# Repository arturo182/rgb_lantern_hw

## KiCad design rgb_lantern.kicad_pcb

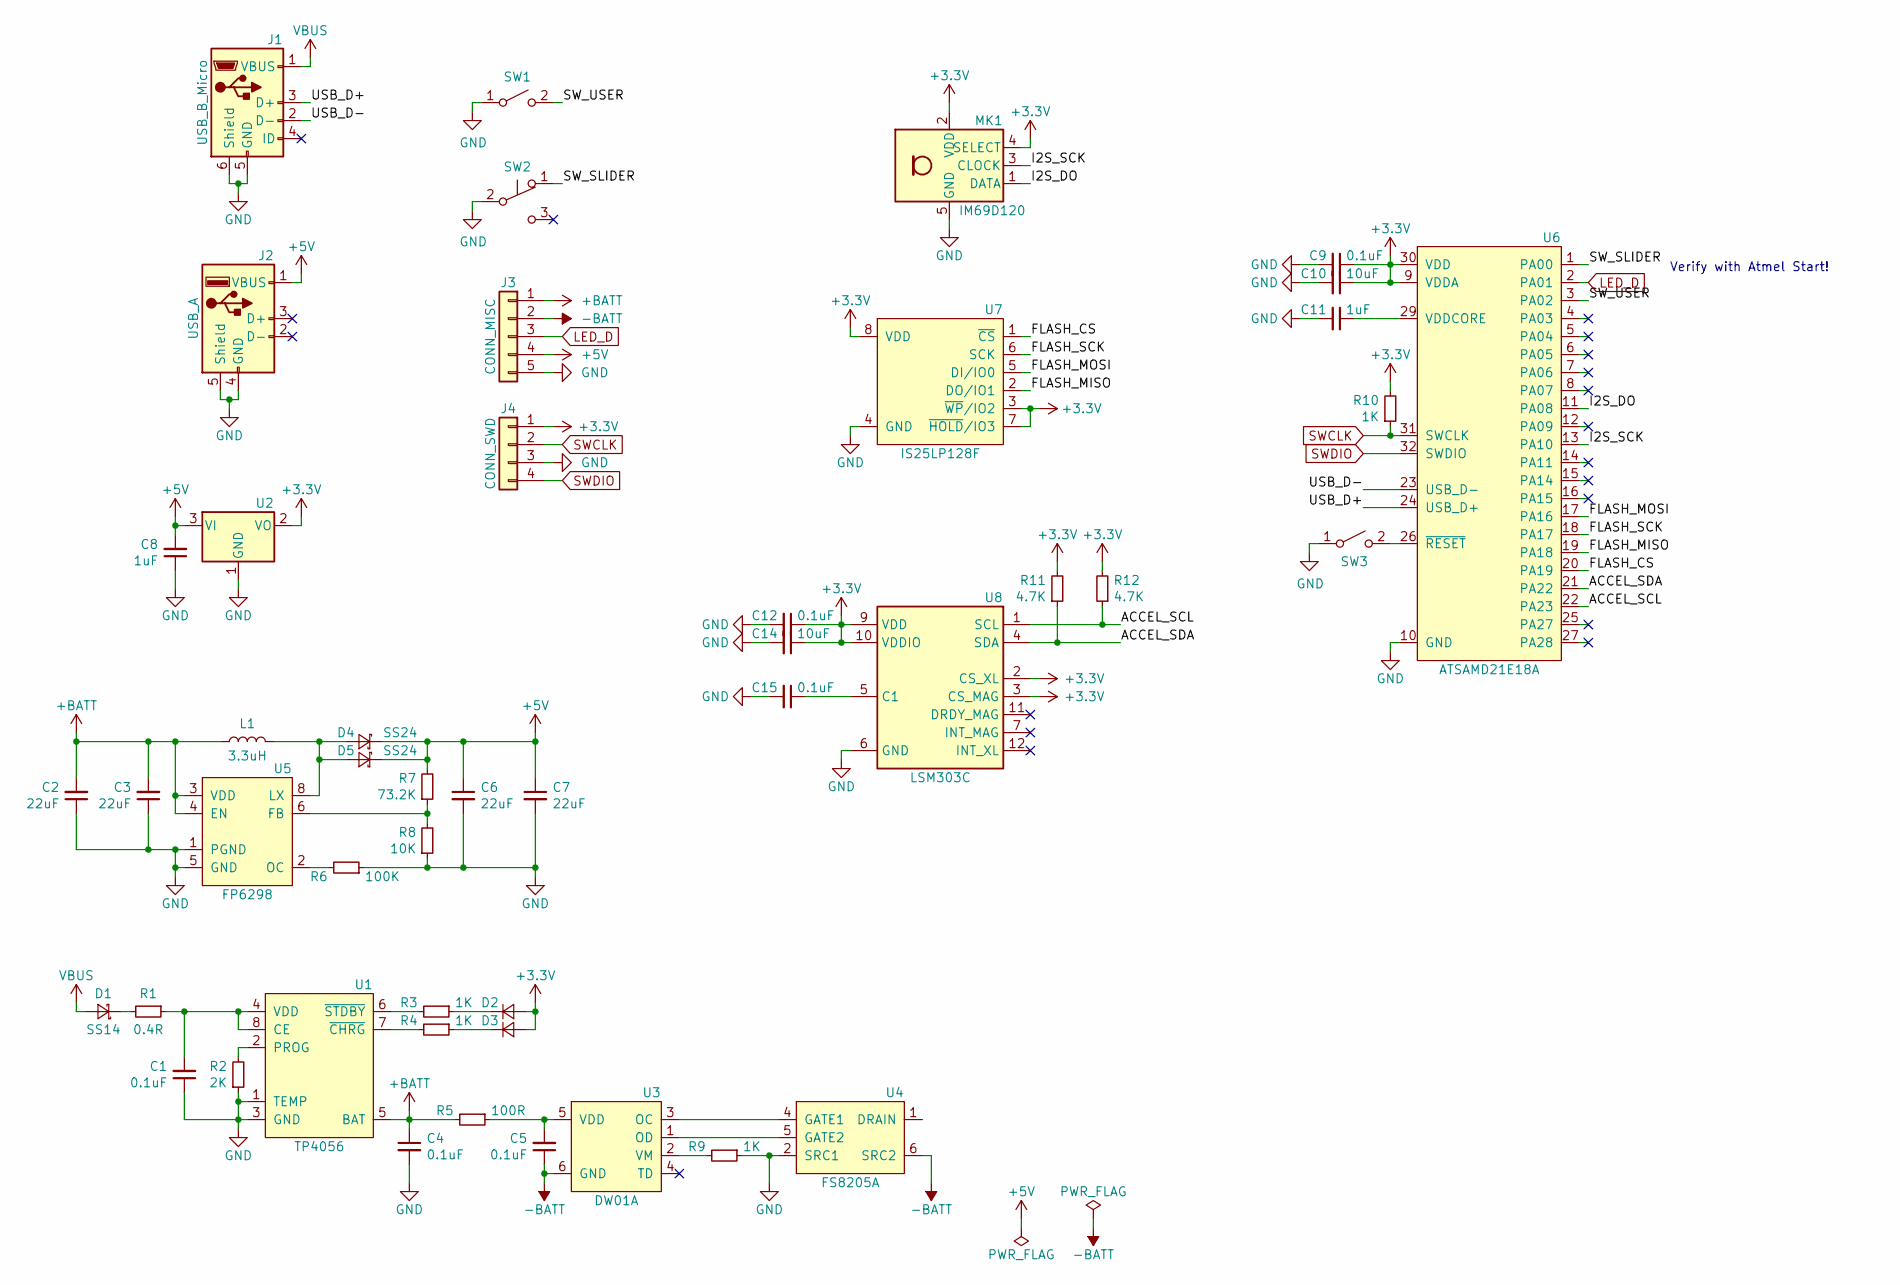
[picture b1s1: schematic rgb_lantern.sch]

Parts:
C1, C4, C5, C9, C12, C15: 0.1uF; C_0603_1608Metric
C2, C3, C6, C7: 22uF; C_0603_1608Metric
C8, C11: 1uF; C_0603_1608Metric
C10, C14: 10uF; C_0603_1608Metric
D1: SS14; D_SMA
D2: D_STDBY; LED_0603_1608Metric
D3: D_CHRG; LED_0603_1608Metric
D4, D5: SS24; D_SMA
J1: USB_B_Micro; USB_Micro-B_Molex-105017-0001
J2: USB_A; USB_A_Stewart_SS-52100-001_Horizontal
J3: CONN_MISC; PinSocket_1x05_P2.54mm_Vertical
J4: CONN_SWD; PinSocket_1x04_P2.54mm_Vertical
L1: 3.3uH; L_Bourns-SRN6028
MK1: IM69D120; Infineon_PG-LLGA-5-1
R1: 0.4R; R_0603_1608Metric
R2: 2K; R_0603_1608Metric
R3, R4, R9, R10: 1K; R_0603_1608Metric
R5: 100R; R_0603_1608Metric
R6: 100K; R_0603_1608Metric
R7: 73.2K; R_0603_1608Metric
R8: 10K; R_0603_1608Metric
R11, R12: 4.7K; R_0603_1608Metric
SW1: SW_USER; SW_Tactile_SPST_Angled_PTS645Vx39-2LFS
SW2: SW_SLIDER; DM1-XXXP-1
SW3: SW_RESET; SW_SPST_B3U-1000P
U1: TP4056; SOP-8-1EP_3.76x4.96mm_P1.27mm_EP2.97x2.18mm
U2: MCP1700-3302E_SOT23; SOT-23
U3: DW01A; SOT-23-6
U4: FS8205A; TSSOP-8_4.4x3mm_P0.65mm
U5: FP6298; SOP-8-1EP_3.76x4.96mm_P1.27mm_EP2.97x2.18mm
U6: ATSAMD21E18A; QFN-32-1EP_5x5mm_P0.5mm_EP3.6x3.6mm
U7: IS25LP128F; WSON-8-1EP_6x5mm_P1.27mm_EP3.4x4mm
U8: LSM303C; LGA-12_2x2mm_P0.5mm

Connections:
+3V3: C9.1, C10.1, C12.1, C14.1, D2.2 (A), D3.2 (A), J4.1, MK1.2 (VDD), MK1.4 (SELECT), R10.2, R11.2, R12.2, U2.2 (VO), U6.9 (VDDA), U6.30 (VDD), U7.3 (~WP~/IO2), U7.7 (~HOLD~/IO3), U7.8 (VDD), U8.2 (CS_XL), U8.3 (CS_MAG), U8.9 (VDD), U8.10 (VDDIO)
+5V: C6.1, C7.1, C8.2, D4.1 (K), D5.1 (K), J2.1 (VBUS), J3.4, R7.2, U2.3 (VI)
+BATT: C2.2, C3.2, C4.1, J3.1, L1.1, R5.2, U1.5 (BAT), U5.3 (VDD), U5.4 (EN)
-BATT: C5.1, J3.2, U3.6 (GND), U4.6 (SRC2), U4.7 (SRC2)
/ACCEL_SCL: R12.1, U6.22 (PA23), U8.1 (SCL)
/ACCEL_SDA: R11.1, U6.21 (PA22), U8.4 (SDA)
/FLASH_CS: U6.20 (PA19), U7.1 (~CS~)
/FLASH_MISO: U6.19 (PA18), U7.2 (DO/IO1)
/FLASH_MOSI: U6.17 (PA16), U7.5 (DI/IO0)
/FLASH_SCK: U6.18 (PA17), U7.6 (SCK)
/I2S_DO: MK1.1 (DATA), U6.11 (PA08)
/I2S_SCK: MK1.3 (CLOCK), U6.13 (PA10)
/SW_SLIDER: SW2.1 (A), U6.1 (PA00)
/SW_USER: SW1.2 (B), U6.3 (PA02)
/USB_D+: J1.3 (D+), U6.24 (USB_D+)
/USB_D-: J1.2 (D-), U6.23 (USB_D-)
GND: C1.1, C2.1, C3.1, C4.2, C6.2, C7.2, C8.1, C9.2, C10.2, C11.2, C12.2, C14.2, C15.2, J1.5 (GND), J1.6 (Shield), J2.4 (GND), J2.5 (Shield), J3.5, J4.3, MK1.5 (GND), R2.1, R6.1, R8.1, R9.1, SW1.1 (A), SW2.2 (B), SW3.1 (A), U1.1 (TEMP), U1.3 (GND), U1.9 (GND), U2.1 (GND), U4.2 (SRC1), U4.3 (SRC1), U5.1 (PGND), U5.5 (GND), U5.9 (GND), U6.10 (GND), U6.28 (GND), U7.4 (GND), U8.6 (GND), U8.8 (GND)
LED_D: J3.3, U6.2 (PA01)
unnamed: C1.2, R1.1, U1.4 (VDD), U1.8 (CE)
unnamed: C5.2, R5.1, U3.5 (VDD)
unnamed: C11.1, U6.29 (VDDCORE)
unnamed: C15.1, U8.5 (C1)
unnamed: D1.1 (K), R1.2
unnamed: D2.1 (K), R3.1
unnamed: D3.1 (K), R4.1
unnamed: D4.2 (A), D5.2 (A), L1.2, U5.8 (LX)
unnamed: R2.2, U1.2 (PROG)
unnamed: R3.2, U1.6 (~STDBY~)
unnamed: R4.2, U1.7 (~CHRG~)
unnamed: R6.2, U5.2 (OC)
unnamed: R7.1, R8.2, U5.6 (FB)
unnamed: R9.2, U3.2 (VM)
unnamed: SW3.2 (B), U6.26 (~RESET~)
unnamed: U3.1 (OD), U4.5 (GATE2)
unnamed: U3.3 (OC), U4.4 (GATE1)
unnamed: U4.1 (DRAIN), U4.8 (DRAIN)
SWCLK: J4.2, R10.1, U6.31 (SWCLK)
SWDIO: J4.4, U6.32 (SWDIO)
VBUS: D1.2 (A), J1.1 (VBUS)

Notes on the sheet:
Verify with Atmel Start!

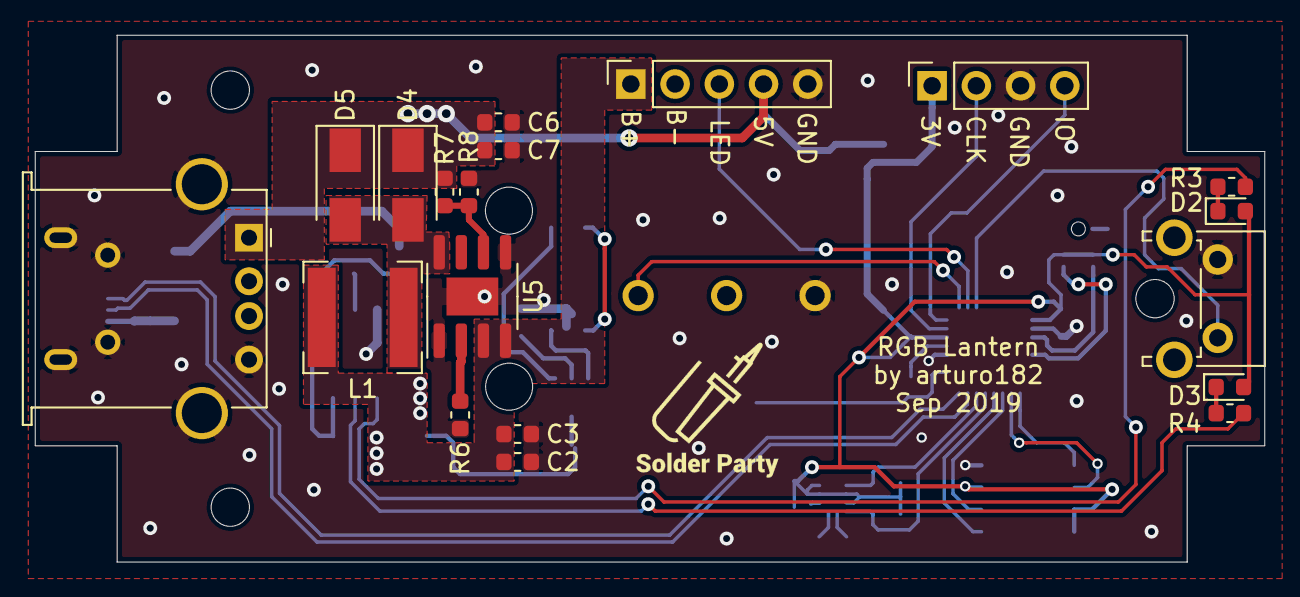
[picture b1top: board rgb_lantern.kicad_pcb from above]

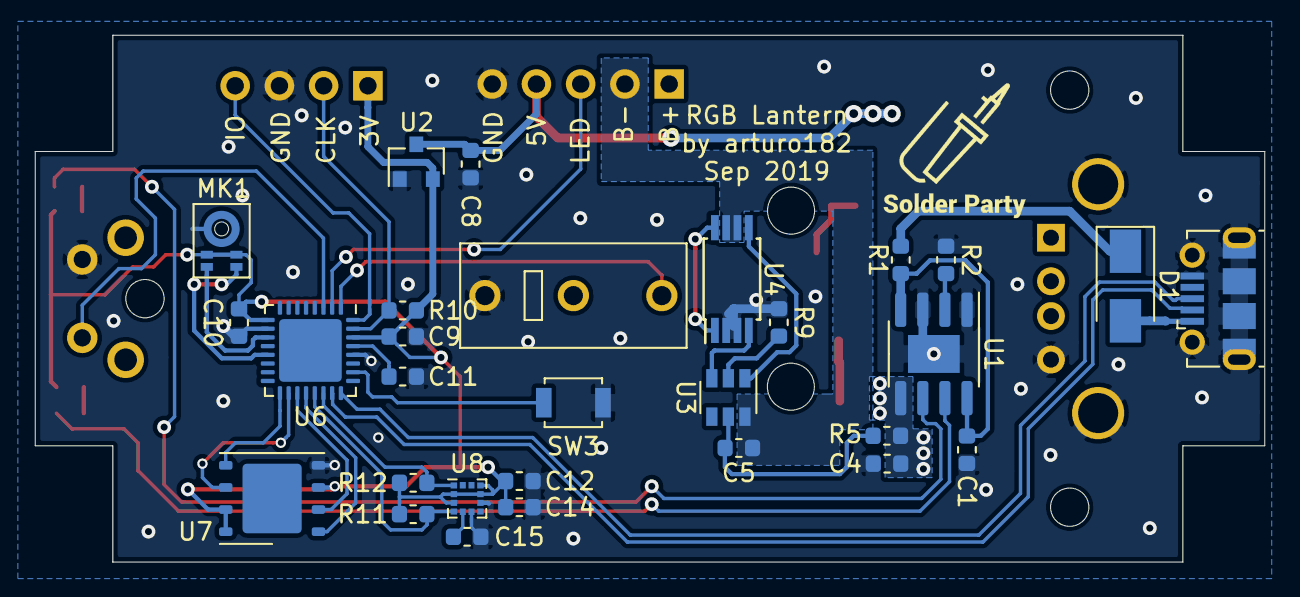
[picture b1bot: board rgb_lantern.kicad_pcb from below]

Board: 2 copper layers, 70.6 x 30.2 mm, 48 parts (29 on the bottom side), 39 nets.

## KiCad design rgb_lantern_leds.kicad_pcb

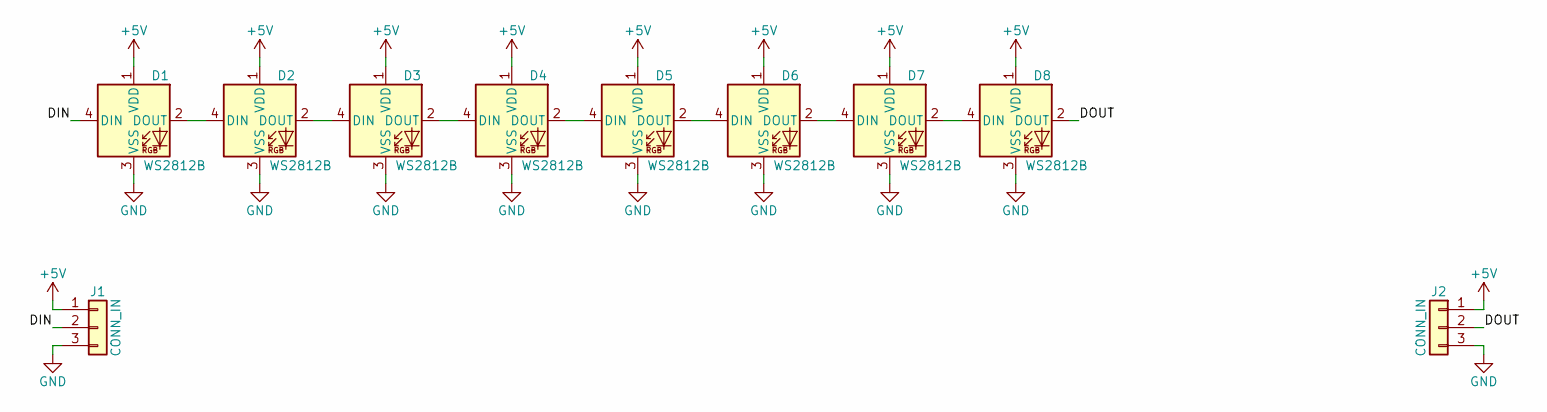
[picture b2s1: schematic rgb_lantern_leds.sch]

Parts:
D1, D2, D3, D4, D5, D6, D7, D8: WS2812B; LED_WS2812B_PLCC4_5.0x5.0mm_P3.2mm
J1, J2: CONN_IN; PinSocket_1x03_P2.54mm_Vertical

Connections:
+5V: D1.1 (VDD), D2.1 (VDD), D3.1 (VDD), D4.1 (VDD), D5.1 (VDD), D6.1 (VDD), D7.1 (VDD), D8.1 (VDD), J1.1, J2.1
/DIN: D1.4 (DIN), J1.2
/DOUT: D8.2 (DOUT), J2.2
GND: D1.3 (VSS), D2.3 (VSS), D3.3 (VSS), D4.3 (VSS), D5.3 (VSS), D6.3 (VSS), D7.3 (VSS), D8.3 (VSS), J1.3, J2.3
unnamed: D1.2 (DOUT), D2.4 (DIN)
unnamed: D2.2 (DOUT), D3.4 (DIN)
unnamed: D3.2 (DOUT), D4.4 (DIN)
unnamed: D4.2 (DOUT), D5.4 (DIN)
unnamed: D5.2 (DOUT), D6.4 (DIN)
unnamed: D6.2 (DOUT), D7.4 (DIN)
unnamed: D7.2 (DOUT), D8.4 (DIN)

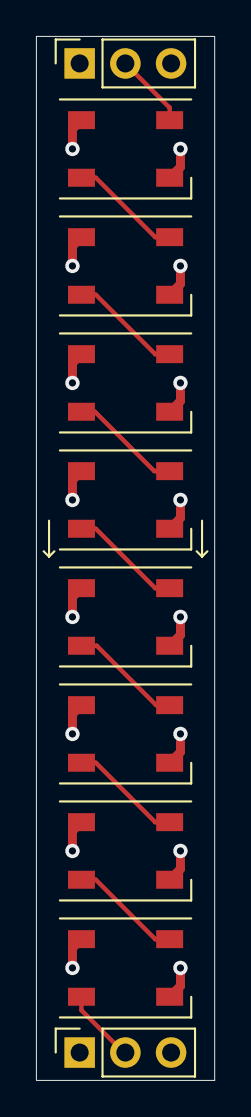
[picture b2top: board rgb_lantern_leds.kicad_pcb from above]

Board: 2 copper layers, 9.9 x 58.0 mm, 10 parts (0 on the bottom side), 11 nets.

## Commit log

2019-10-07 Initial import
